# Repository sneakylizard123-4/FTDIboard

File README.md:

# FTDIboard

FTDIboard is a small USB-to-UART interface that uses the FT232RL and a switchable 3.3V/5V logic rail.

[Finished V1 board](proof/V1/image/IMG_20260908_173817_623.jpg)

---

## Key Features

- FT232RL USB-to-UART bridge
- Switchable 3.3V / 5V logic levels  
- ESP-style auto-reset
- USB ESD protection
- Resettable Fuse (PPTC): 600mA on VBUS 
- Fuse (not resettable): 2.5A fast fuse
- Lots of LEDs
- 75×50mm, 4-layer PCB
- M3 mounting holes
- 2.54mm standard headers

---

## Bill of Materials

| References | Qty | Value | Footprint |
|------------|-----|-------|-----------|
| U3 | 1 | FT232RL | SSOP-28 |
| U2 | 1 | TLV75733PDBV | SOT-23-5 |
| U1 | 1 | USBLC6-2SC6 | SOT-23-6 |
| C1 C4 C5 C7 C8 C10 | 6 | 100nF | 0805 |
| C6 C9 | 2 | 4.7uF | 0805 |
| C2 | 1 | 10uF | 0805 |
| C3 | 1 | 22uF | 0805 |
| R4 R10 R12 R13 R14 R15 R16 R17 R18 R19 R20 R21 R22 R23 R24 R25 | 16 | 10k | 0805 |
| R7 R8 R9 R11 | 4 | 1k | 0805 |
| R3 | 1 | 100k | 0805 |
| R1 R2 | 2 | 5.1k | 0805 |
| R5 R6 | 2 | 33R | 0805 |
| Q2 Q3 | 2 | BC817 | SOT-23 |
| Q1 | 1 | AO3401A | SOT-23 |
| D1 D2 D3 D4 D5 D6 D7 D8 D9 D10 D11 D12 D13 | 13 | LED | 0805 LED |
| J3 | 1 | Conn_01x04 | 1x4 Header 2.54mm |
| J2 | 1 | Conn_01x07 | 1x7 Header 2.54mm |
| J1 | 1 | USB_C_Receptacle_USB2.0_14P | USB-C Receptacle |
| F1 | 1 | 600mA hold, 1.2A trip | Disc 5.1mm |
| F2 | 1 | 2.5A trip | 0603 |
| SW1 | 1 | SW_SPDT_321 | SPDT Slide switch |

*Full BOM available in BOM.csv*

## Usage

1. Connect via USB
2. Install FTDI VCP drivers if needed
3. Select serial port in your IDE
4. Have fun

---

## Images

### PCB Layout

### Schematic

### 3D Model

---

## Testing

v1.1 board built and tested, self-loopback passes clean. the two v1.0 bugbear fixes
(auto-reset latch, VCCIO following the switch) are confirmed gone in this revision.

- v1.1 build + test proof: `proof/V1-1/PROOF.md`
- v1.0 electrical soundness proof: `proof/V1/PROOF.md`

---

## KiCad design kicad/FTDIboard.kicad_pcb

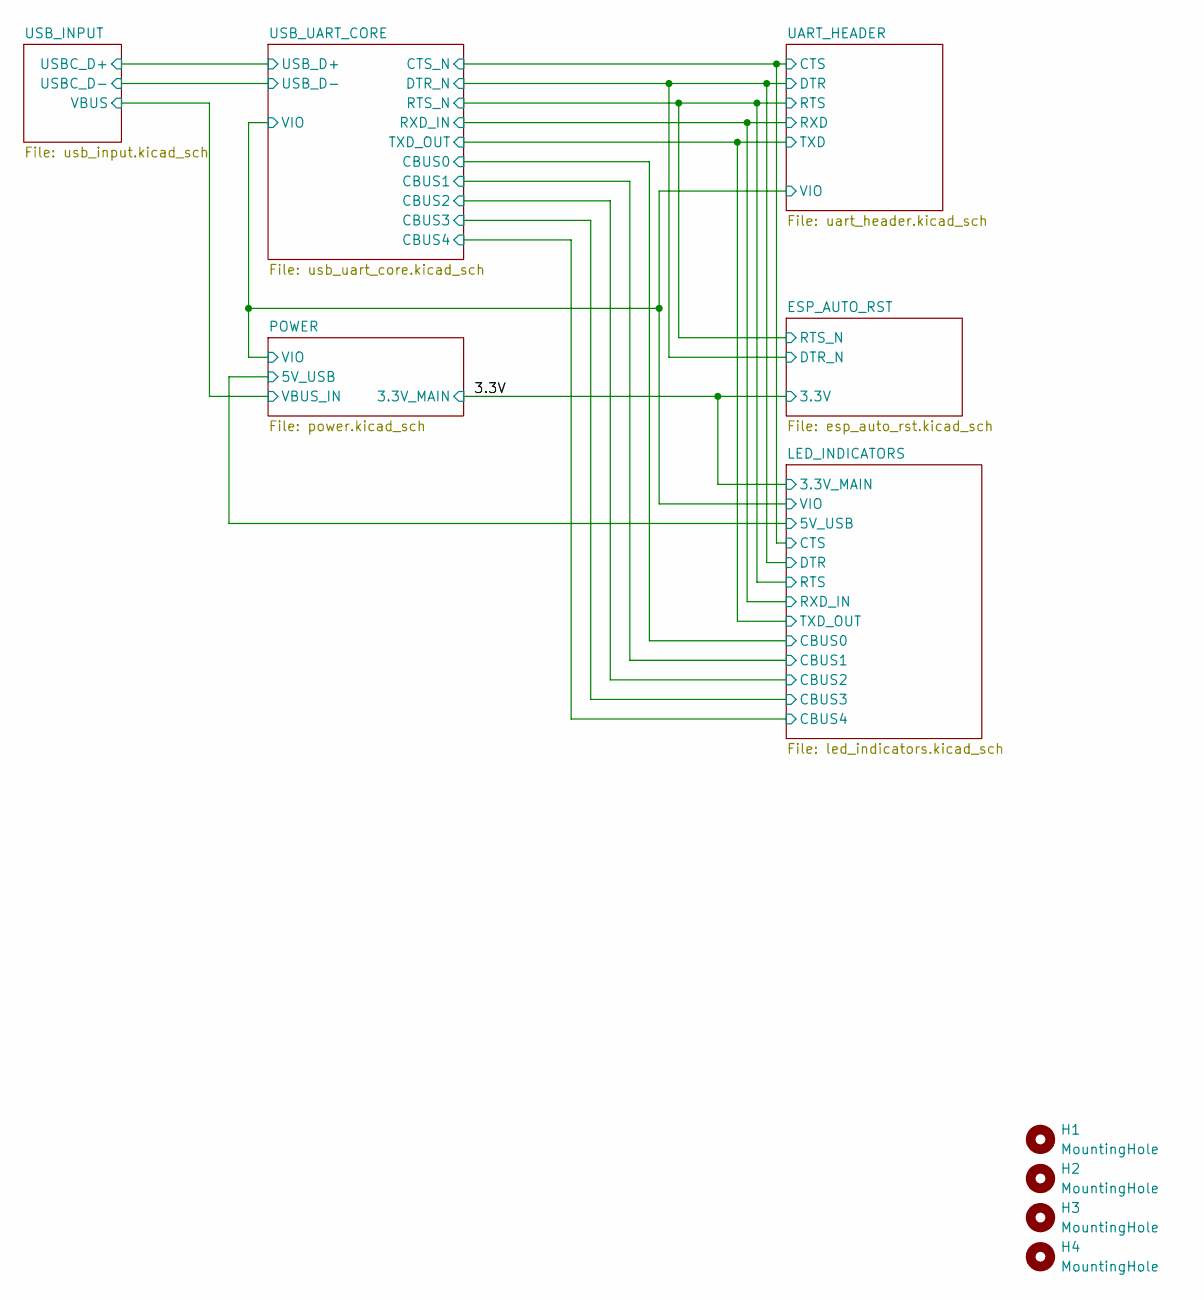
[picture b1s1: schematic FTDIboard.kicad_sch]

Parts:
H1, H2, H3, H4: MountingHole; MountingHole_3.2mm_M3

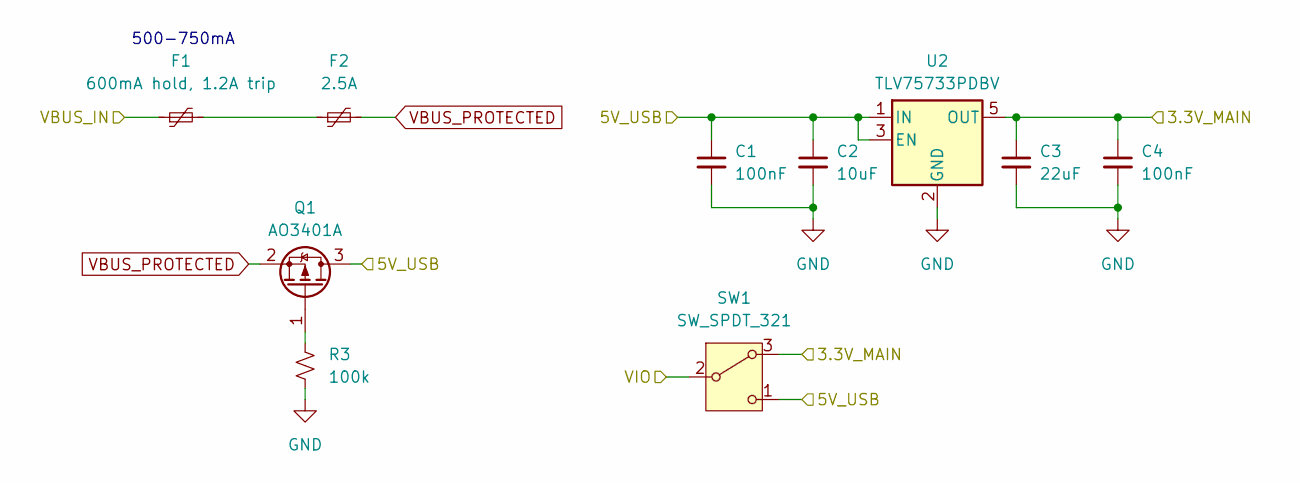
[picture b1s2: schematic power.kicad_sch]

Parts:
C1, C4: 100nF; C_0805_2012Metric_Pad1.18x1.45mm_HandSolder
C2: 10uF; C_0805_2012Metric_Pad1.18x1.45mm_HandSolder
C3: 22uF; C_0805_2012Metric_Pad1.18x1.45mm_HandSolder
F1: 600mA hold, 1.2A trip; C_Disc_D5.1mm_W3.2mm_P5.00mm
F2: 2.5A; Fuse_0603_1608Metric
Q1: AO3401A; SOT-23
R3: 100k; R_0805_2012Metric_Pad1.20x1.40mm_HandSolder
SW1: SW_SPDT_321; SW_Slide_SPDT_Straight_CK_OS102011MS2Q
U2: TLV75733PDBV; SOT-23-5

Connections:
/3.3V: C3.1, C4.1, SW1.3 (A), U2.5 (OUT); also elsewhere on the board
/LED_INDICATORS/5V_USB: C1.1, C2.1, Q1.3 (D), SW1.1 (C), U2.1 (IN), U2.3 (EN); also elsewhere on the board
/LED_INDICATORS/VIO: SW1.2 (B); also elsewhere on the board
/POWER/VBUS_IN: F1.1; also elsewhere on the board
GND: C1.2, C2.2, C3.2, C4.2, R3.2, U2.2 (GND); also elsewhere on the board
unnamed: F1.2, F2.1
unnamed: Q1.1 (G), R3.1
VBUS_PROTECTED: F2.2, Q1.2 (S)

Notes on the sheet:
500-750mA

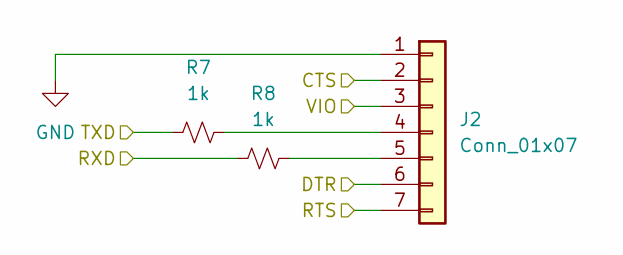
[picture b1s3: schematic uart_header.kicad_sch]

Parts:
J2: Conn_01x07; PinHeader_1x07_P2.54mm_Vertical
R7, R8: 1k; R_0805_2012Metric_Pad1.20x1.40mm_HandSolder

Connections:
/ESP_AUTO_RST/DTR_N: J2.6; also elsewhere on the board
/ESP_AUTO_RST/RTS_N: J2.7; also elsewhere on the board
/LED_INDICATORS/CTS: J2.2; also elsewhere on the board
/LED_INDICATORS/RXD_IN: R8.1; also elsewhere on the board
/LED_INDICATORS/TXD_OUT: R7.1; also elsewhere on the board
/LED_INDICATORS/VIO: J2.3; also elsewhere on the board
GND: J2.1; also elsewhere on the board
unnamed: J2.4, R7.2
unnamed: J2.5, R8.2

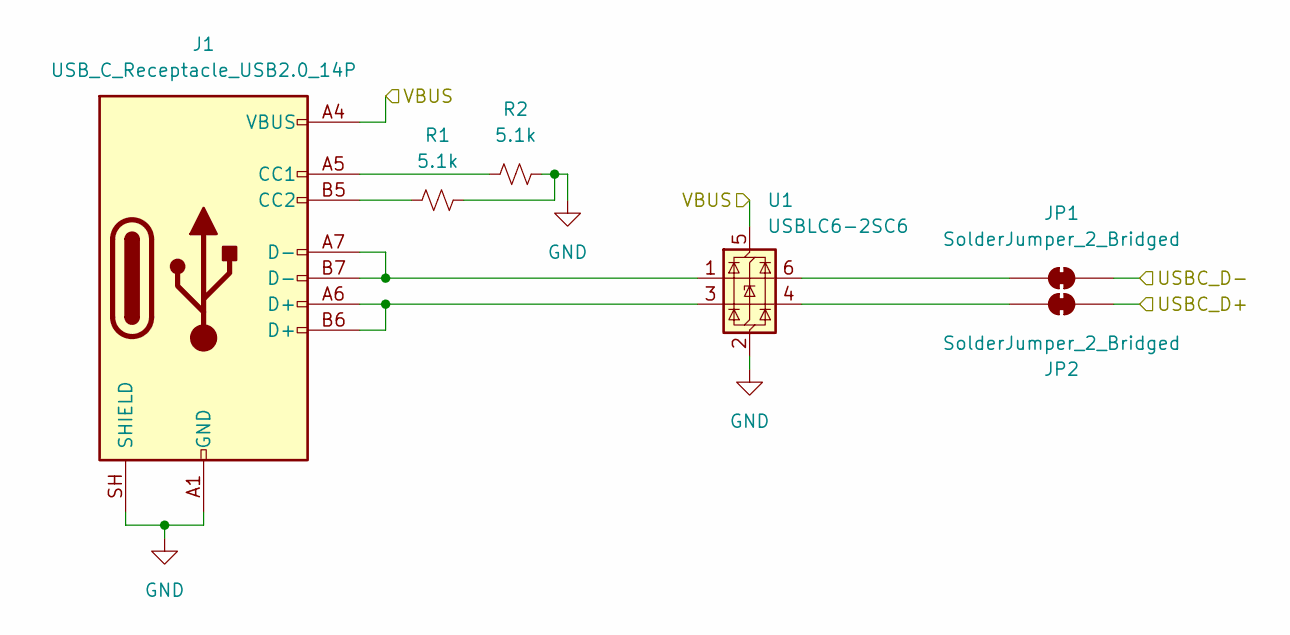
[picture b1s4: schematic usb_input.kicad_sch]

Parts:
J1: USB_C_Receptacle_USB2.0_14P; USB_C_Receptacle_HRO_TYPE-C-31-M-12
JP1, JP2: SolderJumper_2_Bridged; SolderJumper-2_P1.3mm_Bridged_RoundedPad1.0x1.5mm
R1, R2: 5.1k; R_0805_2012Metric_Pad1.20x1.40mm_HandSolder
U1: USBLC6-2SC6; SOT-23-6

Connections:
/POWER/VBUS_IN: J1.A4 (VBUS), J1.A9 (VBUS), J1.B4 (VBUS), J1.B9 (VBUS), U1.5 (VBUS); also elsewhere on the board
/USB_INPUT/USBC_D+: JP2.1 (A); also elsewhere on the board
/USB_INPUT/USBC_D-: JP1.2 (B); also elsewhere on the board
GND: J1.A1 (GND), J1.A12 (GND), J1.B1 (GND), J1.B12 (GND), J1.SH (SHIELD), R1.2, R2.2, U1.2 (GND); also elsewhere on the board
unnamed: J1.A5 (CC1), R2.1
unnamed: J1.B5 (CC2), R1.1
unnamed: J1.A6 (D+), J1.B6 (D+), U1.3 (I/O2)
unnamed: J1.A7 (D-), J1.B7 (D-), U1.1 (I/O1)
unnamed: JP1.1 (A), U1.6 (I/O1)
unnamed: JP2.2 (B), U1.4 (I/O2)

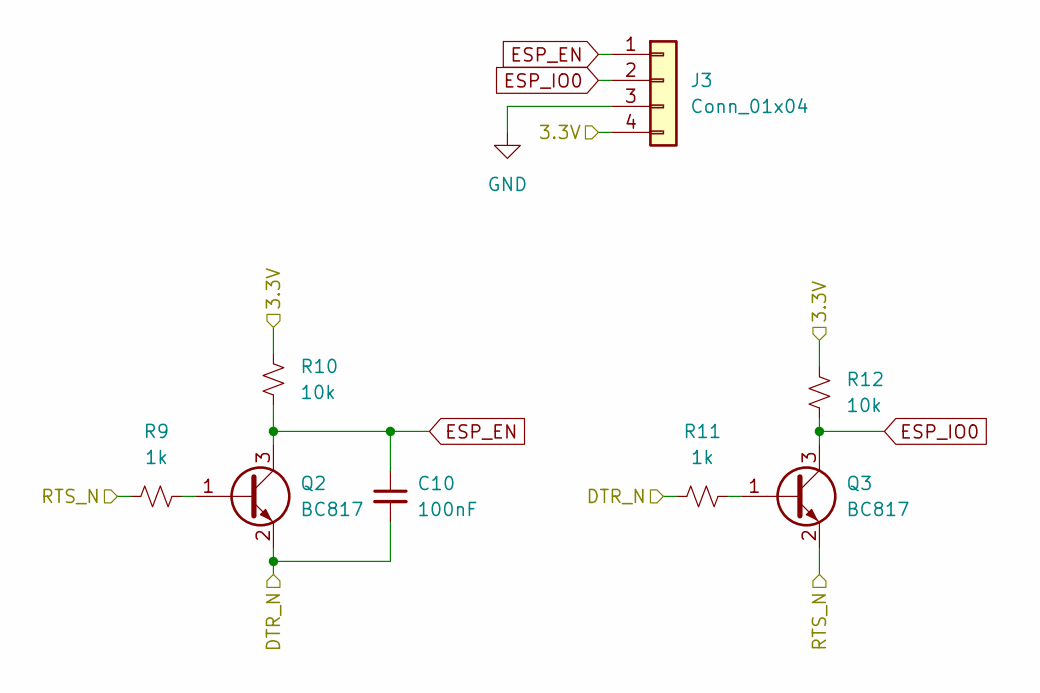
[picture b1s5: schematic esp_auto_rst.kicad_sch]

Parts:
C10: 100nF; C_0805_2012Metric_Pad1.18x1.45mm_HandSolder
J3: Conn_01x04; PinHeader_1x04_P2.54mm_Vertical
Q2, Q3: BC817; SOT-23
R9, R11: 1k; R_0805_2012Metric_Pad1.20x1.40mm_HandSolder
R10, R12: 10k; R_0805_2012Metric_Pad1.20x1.40mm_HandSolder

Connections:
/3.3V: J3.4, R10.1, R12.1; also elsewhere on the board
/ESP_AUTO_RST/DTR_N: C10.2, Q2.2 (E), R11.1; also elsewhere on the board
/ESP_AUTO_RST/RTS_N: Q3.2 (E), R9.1; also elsewhere on the board
ESP_EN: C10.1, J3.1, Q2.3 (C), R10.2
ESP_IO0: J3.2, Q3.3 (C), R12.2
GND: J3.3; also elsewhere on the board
unnamed: Q2.1 (B), R9.2
unnamed: Q3.1 (B), R11.2

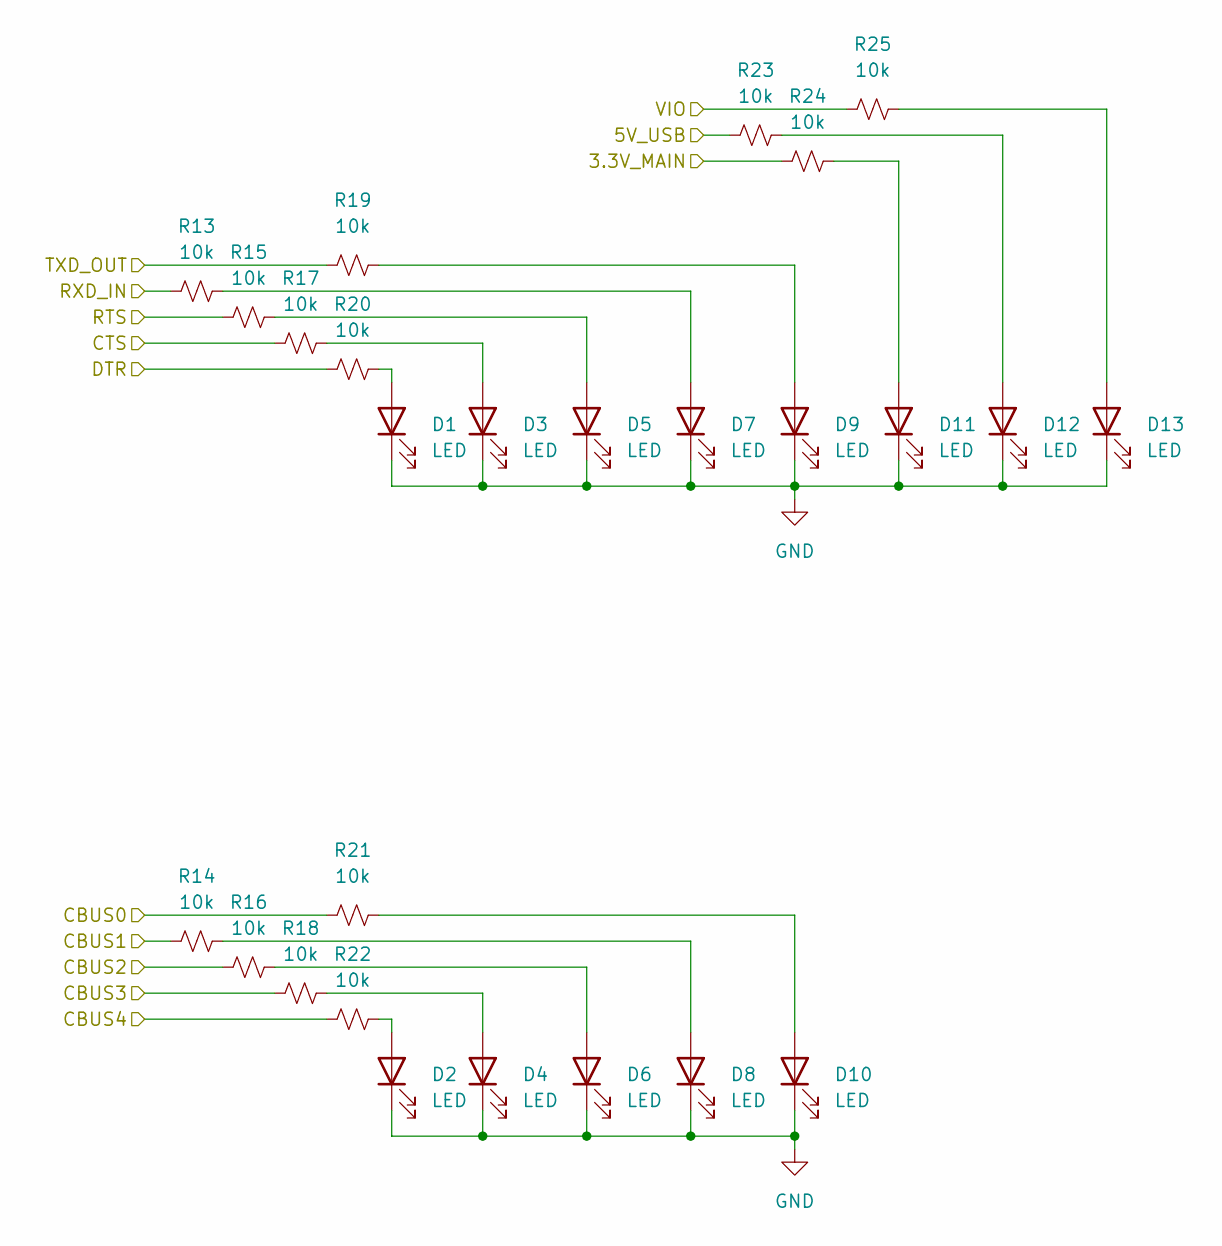
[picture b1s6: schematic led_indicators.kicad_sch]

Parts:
D1, D2, D3, D4, D5, D6, D7, D8, D9, D10, D11, D12, D13: LED; LED_0805_2012Metric_Pad1.15x1.40mm_HandSolder
R13, R14, R15, R16, R17, R18, R19, R20, R21, R22, R23, R24, R25: 10k; R_0805_2012Metric_Pad1.20x1.40mm_HandSolder

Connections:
/3.3V: R24.1; also elsewhere on the board
/ESP_AUTO_RST/DTR_N: R20.1; also elsewhere on the board
/ESP_AUTO_RST/RTS_N: R15.1; also elsewhere on the board
/LED_INDICATORS/5V_USB: R23.1; also elsewhere on the board
/LED_INDICATORS/CBUS0: R21.1; also elsewhere on the board
/LED_INDICATORS/CBUS1: R14.1; also elsewhere on the board
/LED_INDICATORS/CBUS2: R16.1; also elsewhere on the board
/LED_INDICATORS/CBUS3: R18.1; also elsewhere on the board
/LED_INDICATORS/CBUS4: R22.1; also elsewhere on the board
/LED_INDICATORS/CTS: R17.1; also elsewhere on the board
/LED_INDICATORS/RXD_IN: R13.1; also elsewhere on the board
/LED_INDICATORS/TXD_OUT: R19.1; also elsewhere on the board
/LED_INDICATORS/VIO: R25.1; also elsewhere on the board
GND: D1.1 (K), D2.1 (K), D3.1 (K), D4.1 (K), D5.1 (K), D6.1 (K), D7.1 (K), D8.1 (K), D9.1 (K), D10.1 (K), D11.1 (K), D12.1 (K), D13.1 (K); also elsewhere on the board
unnamed: D1.2 (A), R20.2
unnamed: D2.2 (A), R22.2
unnamed: D3.2 (A), R17.2
unnamed: D4.2 (A), R18.2
unnamed: D5.2 (A), R15.2
unnamed: D6.2 (A), R16.2
unnamed: D7.2 (A), R13.2
unnamed: D8.2 (A), R14.2
unnamed: D9.2 (A), R19.2
unnamed: D10.2 (A), R21.2
unnamed: D11.2 (A), R24.2
unnamed: D12.2 (A), R23.2
unnamed: D13.2 (A), R25.2

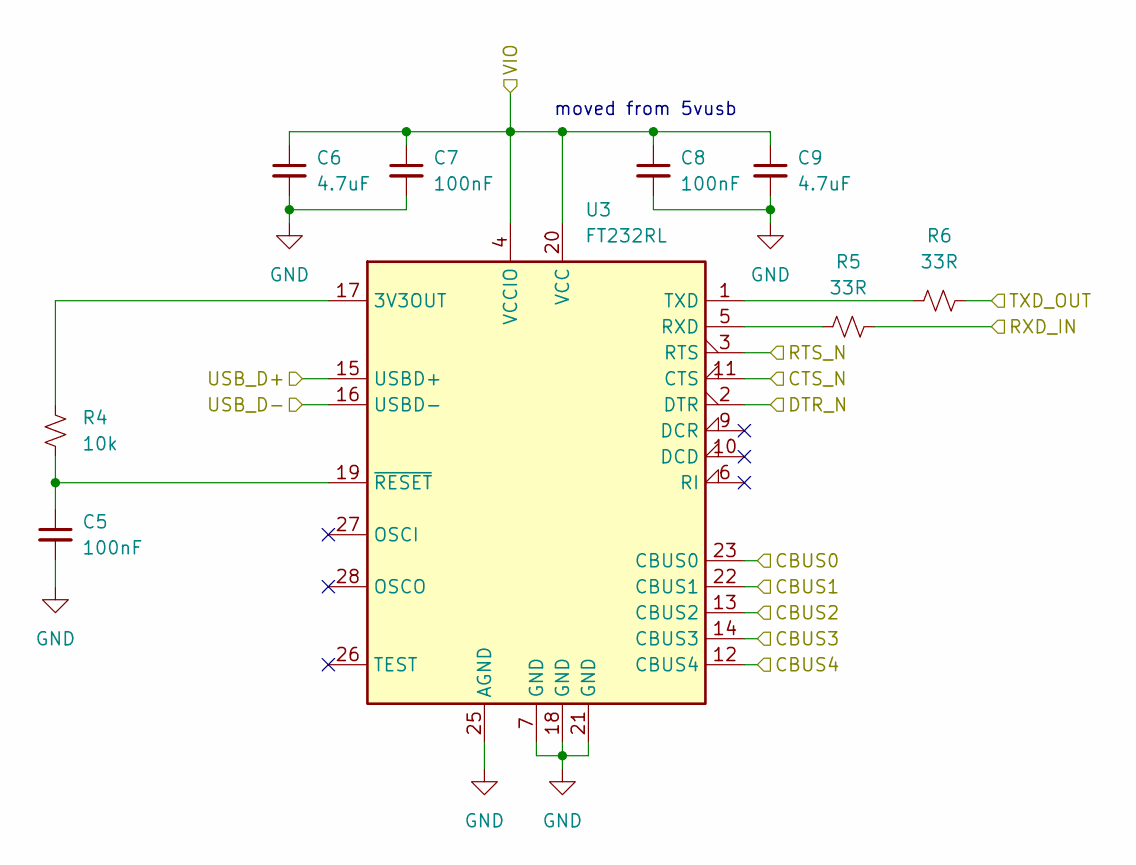
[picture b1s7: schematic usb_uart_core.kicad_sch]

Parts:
C5, C7, C8: 100nF; C_0805_2012Metric_Pad1.18x1.45mm_HandSolder
C6, C9: 4.7uF; C_0805_2012Metric_Pad1.18x1.45mm_HandSolder
R4: 10k; R_0805_2012Metric_Pad1.20x1.40mm_HandSolder
R5, R6: 33R; R_0805_2012Metric_Pad1.20x1.40mm_HandSolder
U3: FT232RL; SSOP-28_5.3x10.2mm_P0.65mm

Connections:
/ESP_AUTO_RST/DTR_N: U3.2 (DTR); also elsewhere on the board
/ESP_AUTO_RST/RTS_N: U3.3 (RTS); also elsewhere on the board
/LED_INDICATORS/CBUS0: U3.23 (CBUS0); also elsewhere on the board
/LED_INDICATORS/CBUS1: U3.22 (CBUS1); also elsewhere on the board
/LED_INDICATORS/CBUS2: U3.13 (CBUS2); also elsewhere on the board
/LED_INDICATORS/CBUS3: U3.14 (CBUS3); also elsewhere on the board
/LED_INDICATORS/CBUS4: U3.12 (CBUS4); also elsewhere on the board
/LED_INDICATORS/CTS: U3.11 (CTS); also elsewhere on the board
/LED_INDICATORS/RXD_IN: R5.2; also elsewhere on the board
/LED_INDICATORS/TXD_OUT: R6.2; also elsewhere on the board
/LED_INDICATORS/VIO: C6.1, C7.1, C8.1, C9.1, U3.4 (VCCIO), U3.20 (VCC); also elsewhere on the board
/USB_INPUT/USBC_D+: U3.15 (USBD+); also elsewhere on the board
/USB_INPUT/USBC_D-: U3.16 (USBD-); also elsewhere on the board
GND: C5.2, C6.2, C7.2, C8.2, C9.2, U3.7 (GND), U3.18 (GND), U3.21 (GND), U3.25 (AGND); also elsewhere on the board
unnamed: R4.1, U3.17 (3V3OUT)
unnamed: R5.1, U3.5 (RXD)
unnamed: R6.1, U3.1 (TXD)
unnamed: C5.1, R4.2, U3.19 (~RESET)

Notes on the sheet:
moved from 5vusb

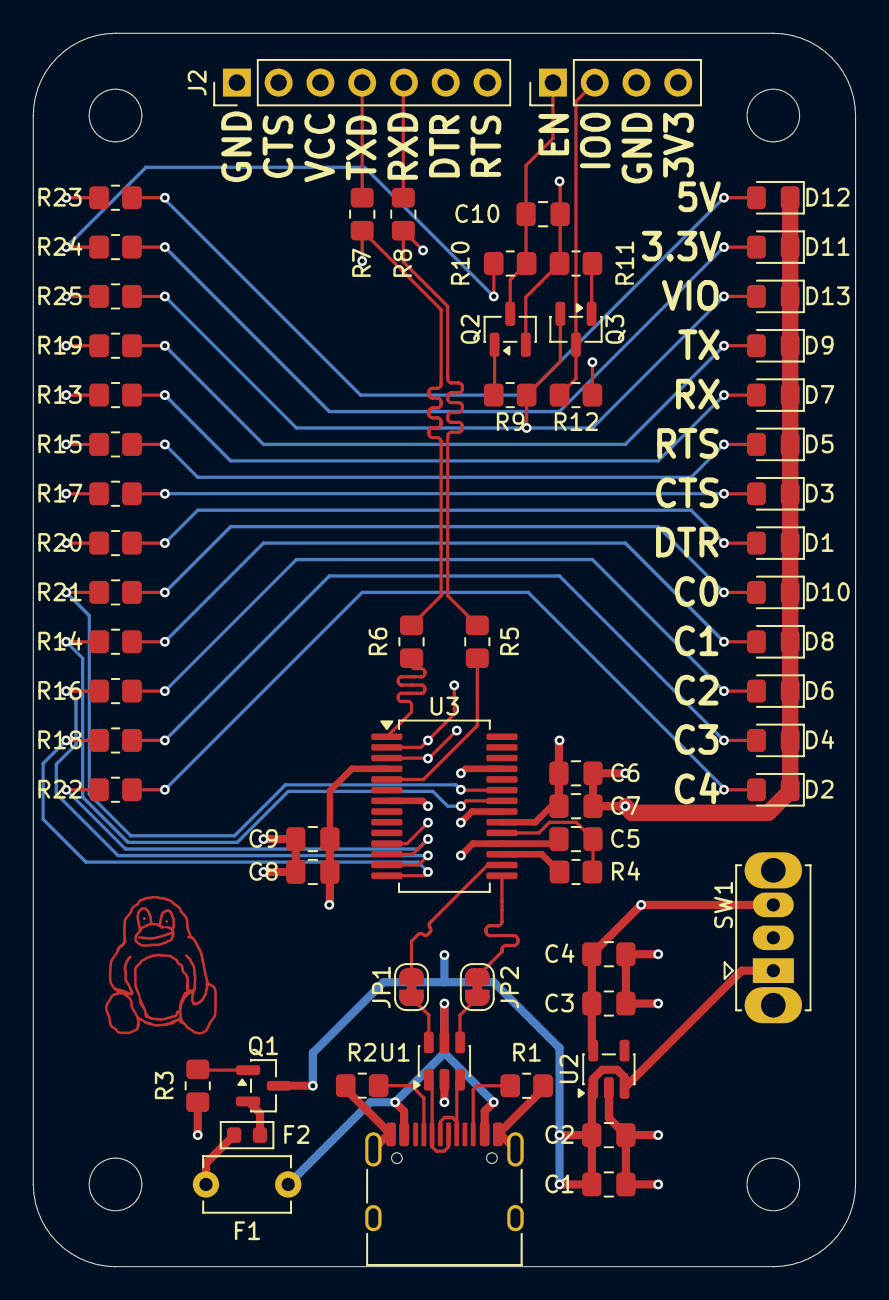
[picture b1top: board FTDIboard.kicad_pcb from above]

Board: 4 copper layers, 50.0 x 75.0 mm, 66 parts (0 on the bottom side), 49 nets.

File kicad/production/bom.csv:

Designator,Footprint,Quantity,Value,LCSC Part #
"C1, C10, C4, C5, C7, C8",0805,6,100nF,
C2,0805,1,10uF,
C3,0805,1,22uF,
"C6, C9",0805,2,4.7uF,
"D1, D10, D11, D12, D13, D2, D3, D4, D5, D6, D7, D8, D9",0805,13,LED,
F1,C_Disc_D5.1mm_W3.2mm_P5.00mm,1,"600mA hold, 1.2A trip",
F2,0603,1,2.5A,
J1,USB_C_Receptacle_HRO_TYPE-C-31-M-12,1,USB_C_Receptacle_USB2.0_14P,
J2,PinHeader_1x07_P2.54mm_Vertical,1,Conn_01x07,
J3,PinHeader_1x04_P2.54mm_Vertical,1,Conn_01x04,
Q1,SOT-23,1,AO3401A,
"Q2, Q3",SOT-23,2,BC817,
"R1, R2",0805,2,5.1k,
"R10, R12, R13, R14, R15, R16, R17, R18, R19, R20, R21, R22, R23, R24, R25, R4",0805,16,10k,
"R11, R7, R8, R9",0805,4,1k,
R3,0805,1,100k,
"R5, R6",0805,2,33R,
SW1,SW_Slide_SPDT_Straight_CK_OS102011MS2Q,1,SW_SPDT_321,
U1,SOT-23-6,1,USBLC6-2SC6,
U2,SOT-23-5,1,TLV75733PDBV,
U3,SSOP-28_5.3x10.2mm_P0.65mm,1,FT232RL,

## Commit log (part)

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2026-06-19 whee!
2026-06-21 readme
2026-06-22 add journal and some more logos and pictograms
2026-06-22 rename JOURNAL
2026-06-22 renames
2026-06-22 add images and jourlnal
2026-06-22 journal
2026-06-24 rename
2026-06-24 blender updates!
2026-06-24 bom updates
2026-06-24 readme updapte
2026-06-24 fix gitignore to include schematics
2026-06-24 fix images
2026-06-24 blender upates
2026-06-25 update bom
2026-06-25 bom update
2026-06-25 add pcbway stuff
2026-06-25 add jlcpcb
2026-06-25 add pcbs to bom and notes
2026-06-25 adsaffffffffff
2026-06-26 blenders
